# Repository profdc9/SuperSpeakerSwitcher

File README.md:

# Stereo Super Speaker Switcher

This is a two-channel PCB layout for a heavy duty relay-based speaker switcher by Daniel Marks.  The project is licensed under Creative Commons CC-BY-SA 4.0.

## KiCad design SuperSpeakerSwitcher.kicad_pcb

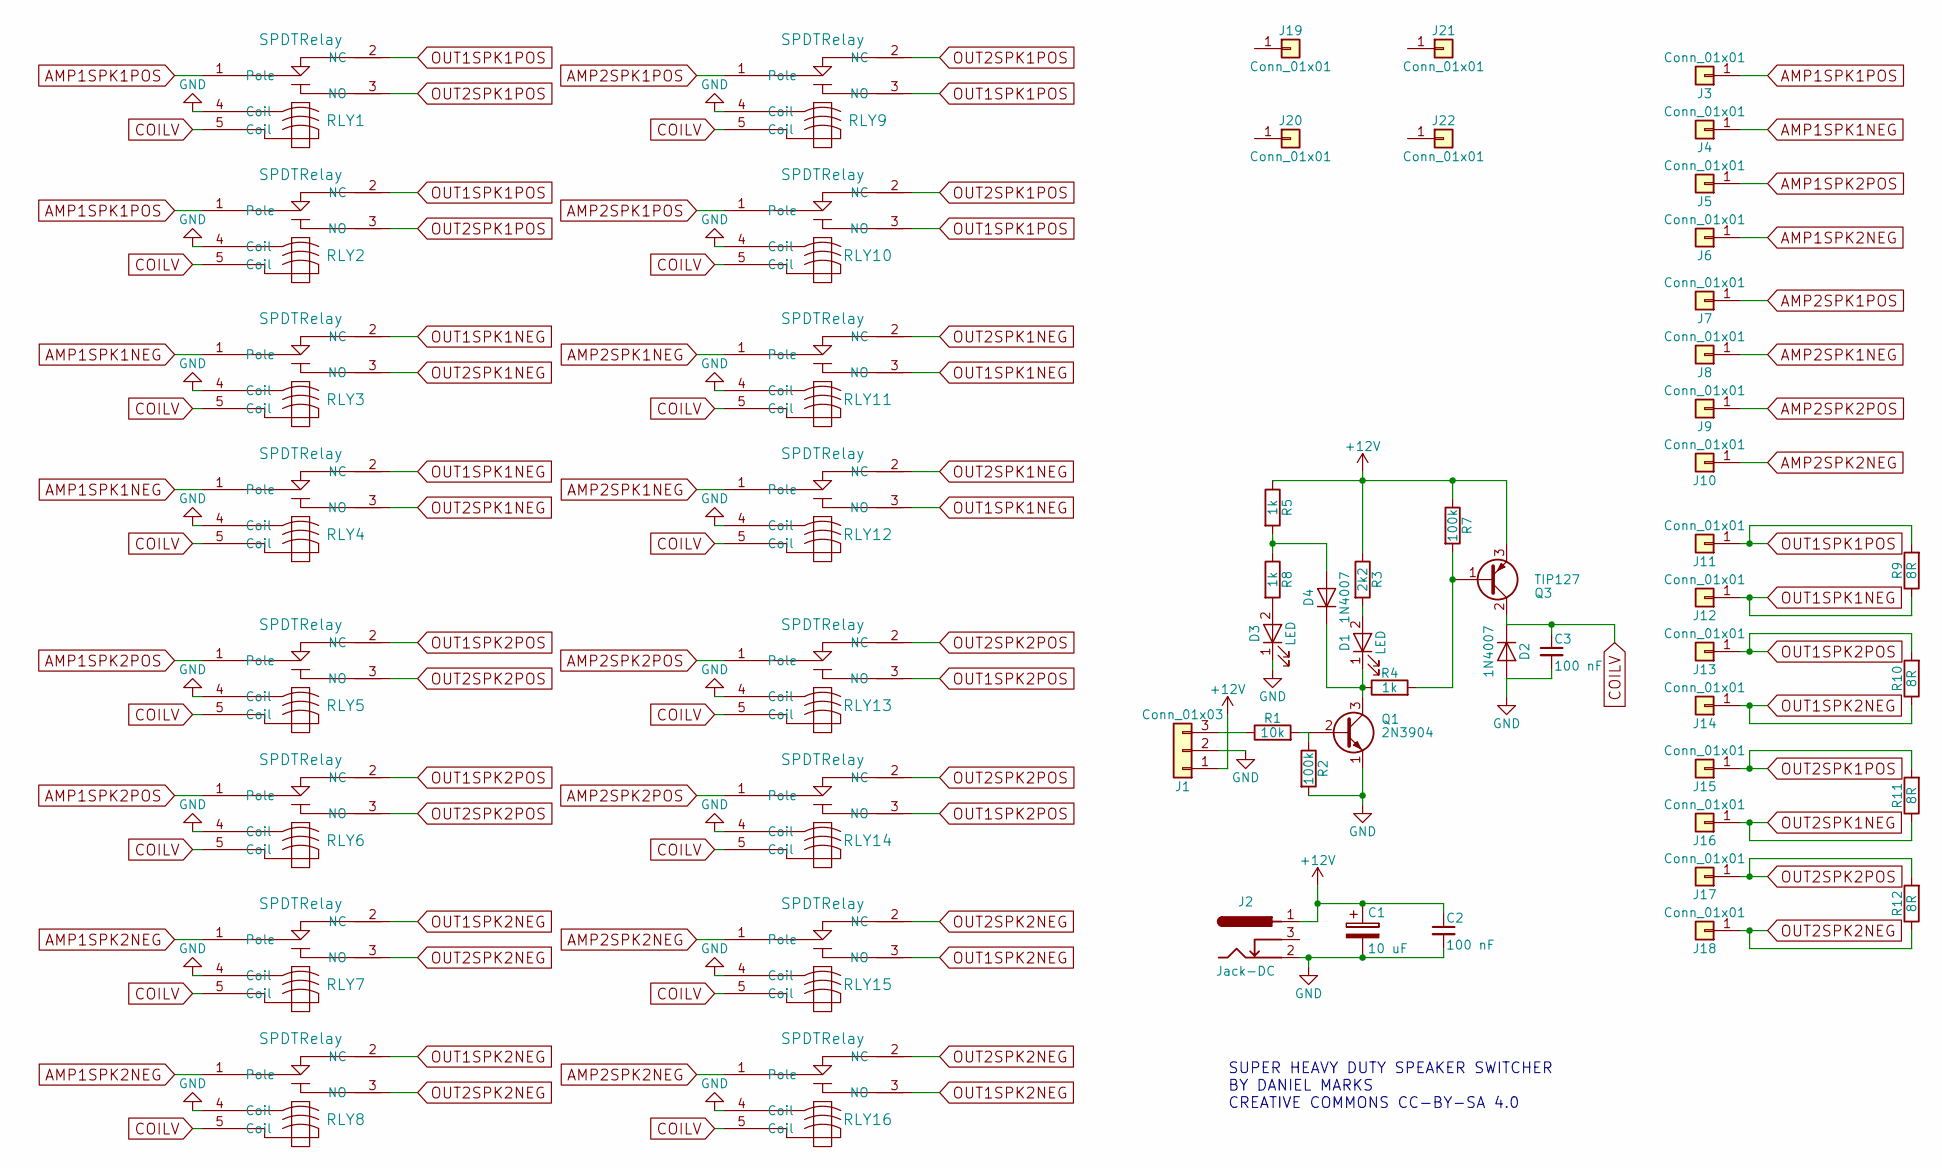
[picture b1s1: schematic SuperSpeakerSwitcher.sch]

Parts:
C1: 10 uF; CP_Radial_D5.0mm_P2.50mm
C2, C3: 100 nF; C_Disc_D5.0mm_W2.5mm_P5.00mm
D1, D3: LED; LED_D5.0mm
D2, D4: 1N4007; D_DO-41_SOD81_P7.62mm_Horizontal
J1: Conn_01x03; TerminalBlock_bornier-3_P5.08mm
J2: Jack-DC; BARREL_JACK
J3, J4, J5, J6, J7, J8, J9, J10, J11, J12, J13, J14, J15, J16, J17, J18: Conn_01x01; SpadeTerminal635
J19, J20, J21, J22: Conn_01x01; 1pin
Q1: 2N3904; TO-92_Inline_Wide
Q3: TIP127; TO-220-3_Vertical
R1: 10k; R_Axial_DIN0207_L6.3mm_D2.5mm_P7.62mm_Horizontal
R2, R7: 100k; R_Axial_DIN0207_L6.3mm_D2.5mm_P7.62mm_Horizontal
R3: 2k2; R_Axial_DIN0207_L6.3mm_D2.5mm_P7.62mm_Horizontal
R4, R5, R8: 1k; R_Axial_DIN0207_L6.3mm_D2.5mm_P7.62mm_Horizontal
R9, R10, R11, R12: 8R; R_Axial_Power_L20.0mm_W6.4mm_P25.40mm
RLY1, RLY2, RLY3, RLY4, RLY5, RLY6, RLY7, RLY8, RLY9, RLY10, RLY11, RLY12, RLY13, RLY14, RLY15, RLY16: SPDTRelay; SMIHRelay

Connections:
+12V: C1.1, C2.1, J1.1, J2.1, Q3.3 (E), R3.1, R5.1, R7.1
AMP1SPK1NEG: J4.1, RLY3.1 (Pole), RLY4.1 (Pole)
AMP1SPK1POS: J3.1, RLY1.1 (Pole), RLY2.1 (Pole)
AMP1SPK2NEG: J6.1, RLY7.1 (Pole), RLY8.1 (Pole)
AMP1SPK2POS: J5.1, RLY5.1 (Pole), RLY6.1 (Pole)
AMP2SPK1NEG: J8.1, RLY11.1 (Pole), RLY12.1 (Pole)
AMP2SPK1POS: J7.1, RLY9.1 (Pole), RLY10.1 (Pole)
AMP2SPK2NEG: J10.1, RLY15.1 (Pole), RLY16.1 (Pole)
AMP2SPK2POS: J9.1, RLY13.1 (Pole), RLY14.1 (Pole)
COILV: C3.1, D2.1 (K), Q3.2 (C), RLY1.5 (Coil), RLY2.5 (Coil), RLY3.5 (Coil), RLY4.5 (Coil), RLY5.5 (Coil), RLY6.5 (Coil), RLY7.5 (Coil), RLY8.5 (Coil), RLY9.5 (Coil), RLY10.5 (Coil), RLY11.5 (Coil), RLY12.5 (Coil), RLY13.5 (Coil), RLY14.5 (Coil), RLY15.5 (Coil), RLY16.5 (Coil)
GND: C1.2, C2.2, C3.2, D2.2 (A), D3.1 (K), J1.2, J2.2, Q1.1 (E), R2.2, RLY1.4 (Coil), RLY2.4 (Coil), RLY3.4 (Coil), RLY4.4 (Coil), RLY5.4 (Coil), RLY6.4 (Coil), RLY7.4 (Coil), RLY8.4 (Coil), RLY9.4 (Coil), RLY10.4 (Coil), RLY11.4 (Coil), RLY12.4 (Coil), RLY13.4 (Coil), RLY14.4 (Coil), RLY15.4 (Coil), RLY16.4 (Coil)
unnamed: D1.1 (K), D4.1 (K), Q1.3 (C), R4.1
unnamed: D1.2 (A), R3.2
unnamed: D3.2 (A), R8.2
unnamed: D4.2 (A), R5.2, R8.1
unnamed: J1.3, R1.1
unnamed: Q1.2 (B), R1.2, R2.1
unnamed: Q3.1 (B), R4.2, R7.2
OUT1SPK1NEG: J12.1, R9.1, RLY3.2 (NC), RLY4.2 (NC), RLY11.3 (NO), RLY12.3 (NO)
OUT1SPK1POS: J11.1, R9.2, RLY1.2 (NC), RLY2.2 (NC), RLY9.3 (NO), RLY10.3 (NO)
OUT1SPK2NEG: J14.1, R10.1, RLY7.2 (NC), RLY8.2 (NC), RLY15.3 (NO), RLY16.3 (NO)
OUT1SPK2POS: J13.1, R10.2, RLY5.2 (NC), RLY6.2 (NC), RLY13.3 (NO), RLY14.3 (NO)
OUT2SPK1NEG: J16.1, R11.1, RLY3.3 (NO), RLY4.3 (NO), RLY11.2 (NC), RLY12.2 (NC)
OUT2SPK1POS: J15.1, R11.2, RLY1.3 (NO), RLY2.3 (NO), RLY9.2 (NC), RLY10.2 (NC)
OUT2SPK2NEG: J18.1, R12.1, RLY7.3 (NO), RLY8.3 (NO), RLY15.2 (NC), RLY16.2 (NC)
OUT2SPK2POS: J17.1, R12.2, RLY5.3 (NO), RLY6.3 (NO), RLY13.2 (NC), RLY14.2 (NC)

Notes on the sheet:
SUPER HEAVY DUTY SPEAKER SWITCHER BY DANIEL MARKS CREATIVE COMMONS CC-BY-SA 4.0

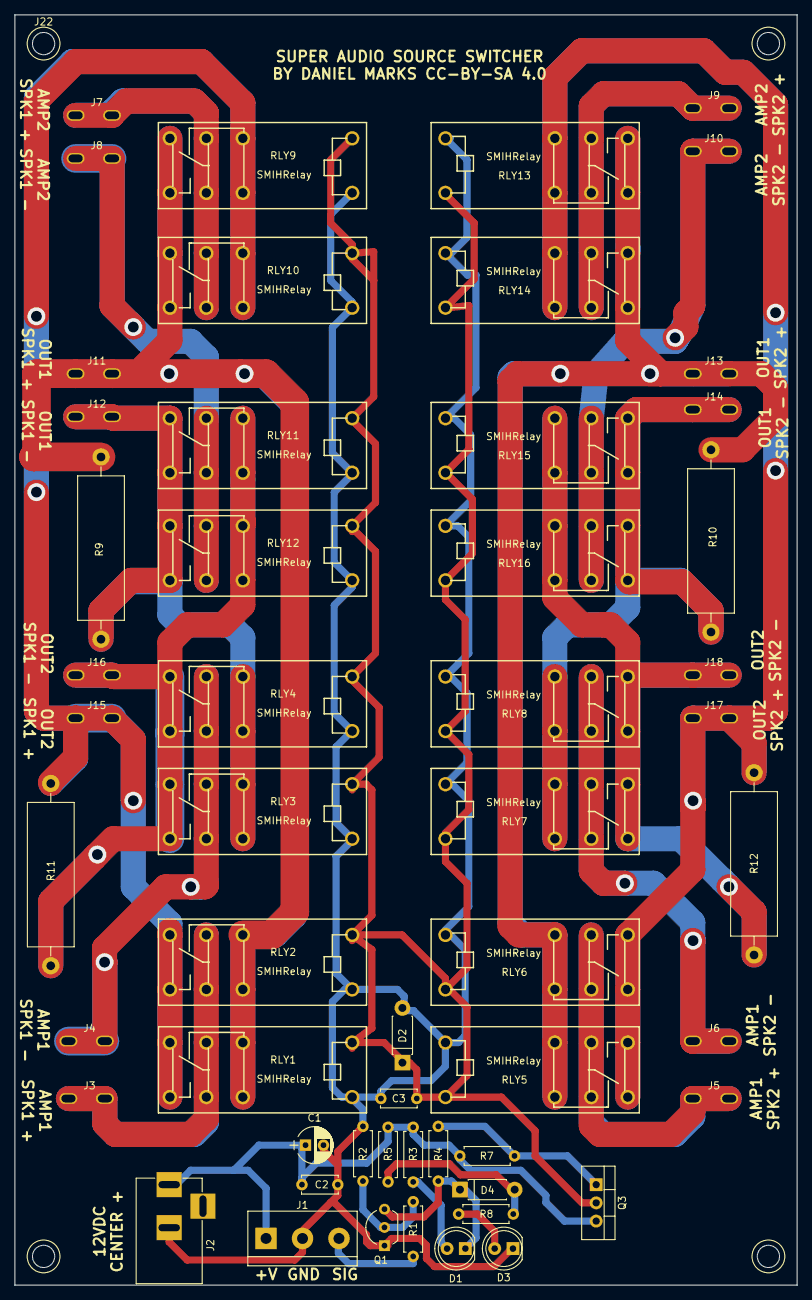
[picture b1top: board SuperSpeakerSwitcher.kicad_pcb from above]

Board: 2 copper layers, 109.0 x 177.0 mm, 58 parts (0 on the bottom side), 26 nets.

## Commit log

2020-11-01 Bulked up the traces
2020-11-12 Fixed on and off diodes

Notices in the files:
SuperSpeakerSwitcher.kicad_pcb:
BY DANIEL MARKS CC-BY-SA 4.0
